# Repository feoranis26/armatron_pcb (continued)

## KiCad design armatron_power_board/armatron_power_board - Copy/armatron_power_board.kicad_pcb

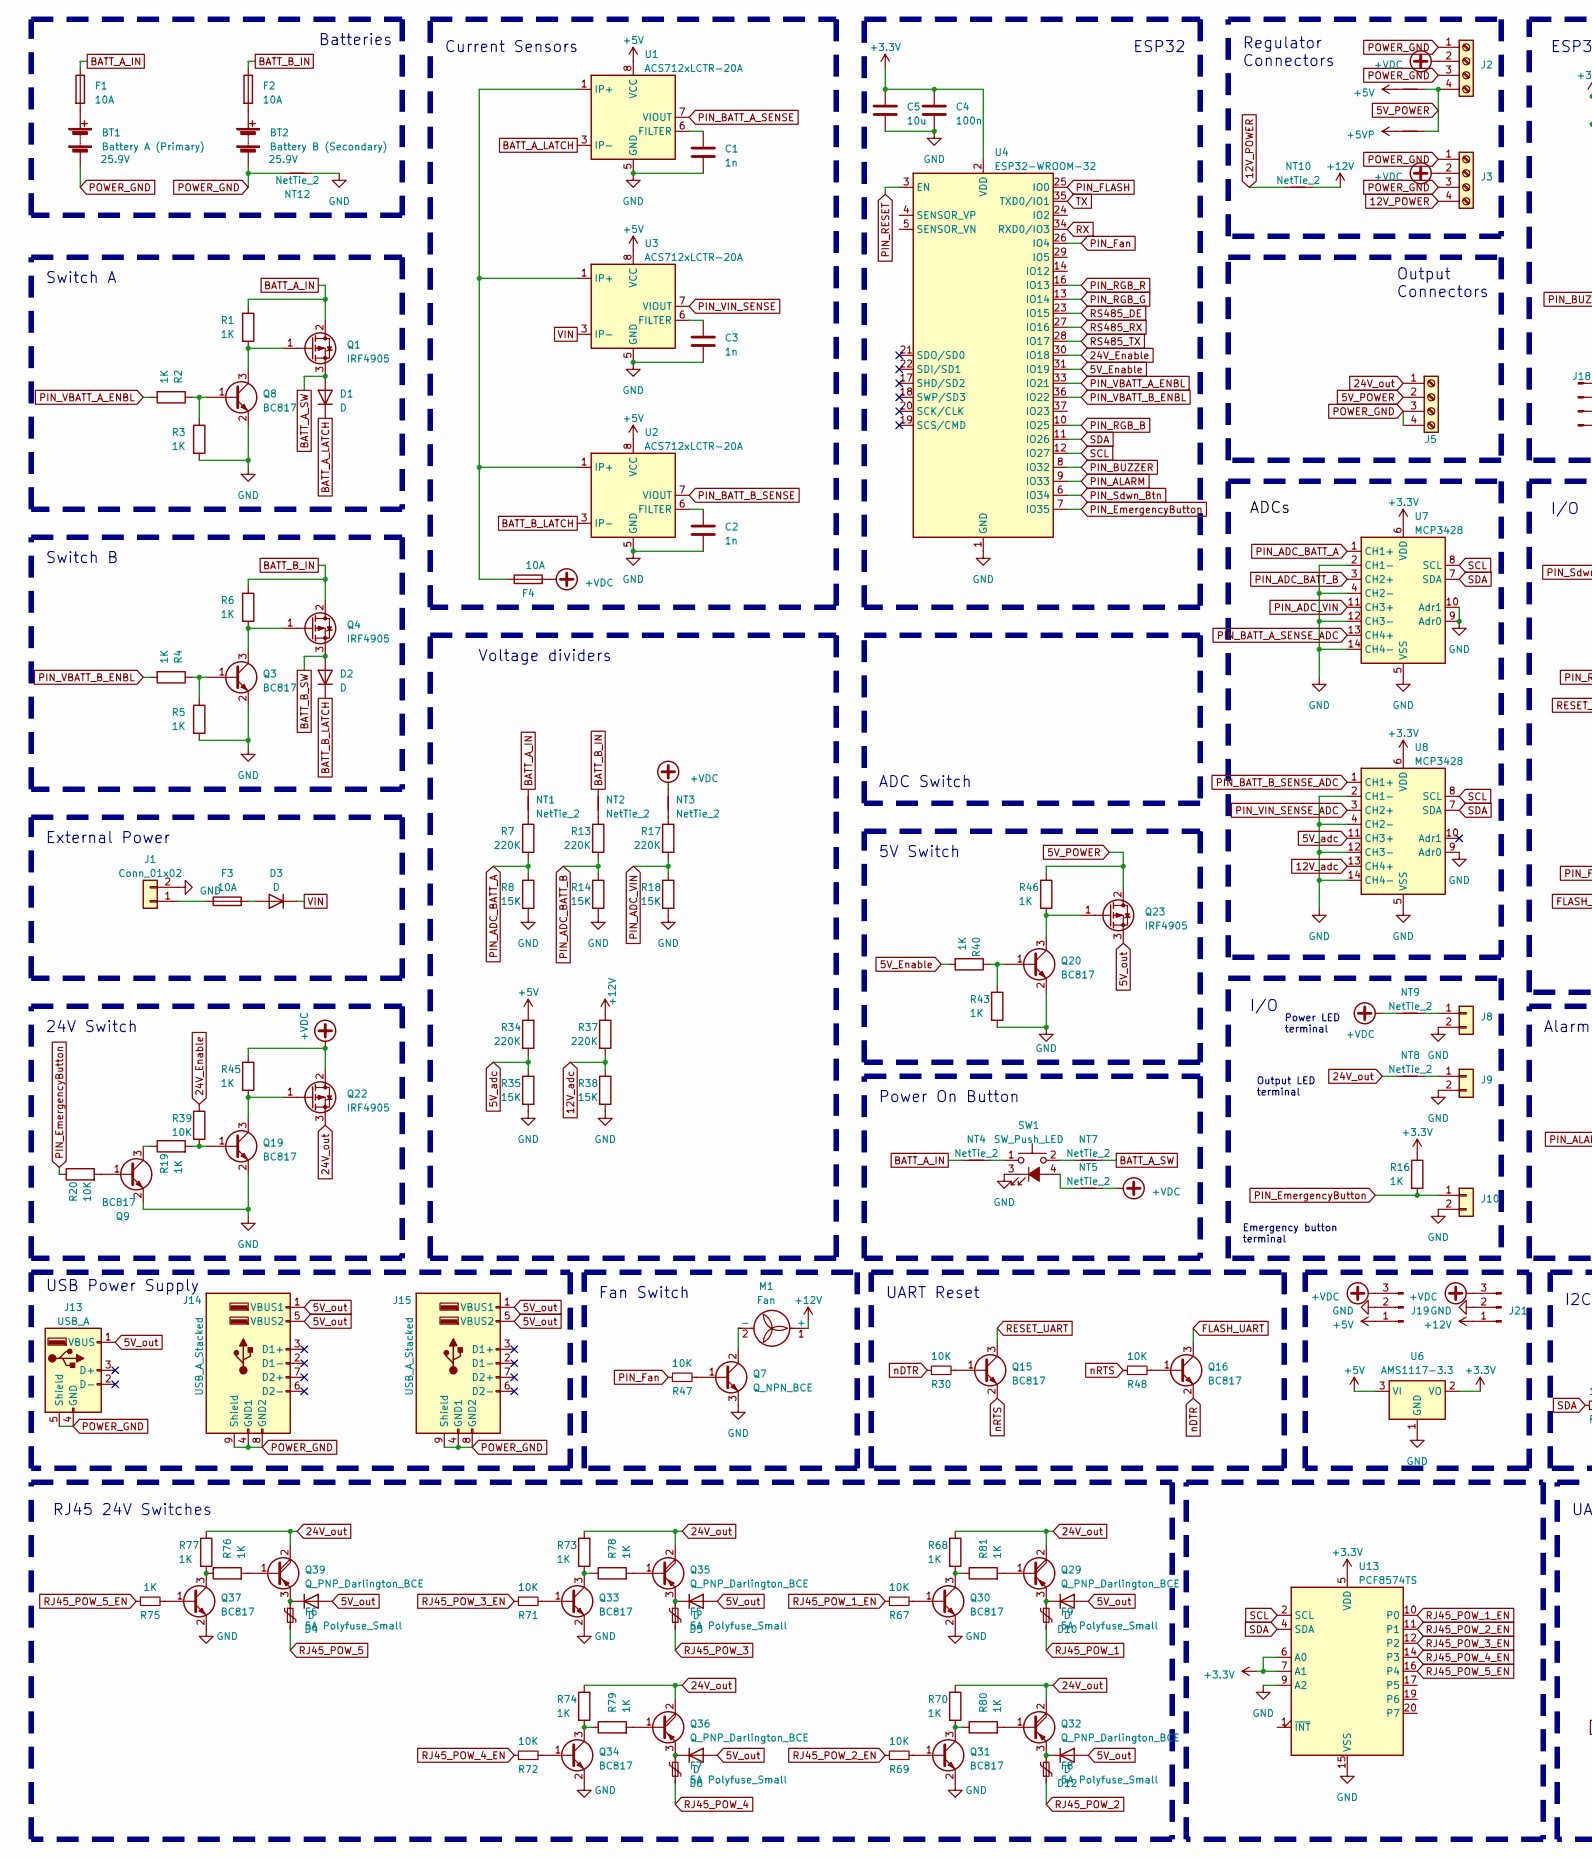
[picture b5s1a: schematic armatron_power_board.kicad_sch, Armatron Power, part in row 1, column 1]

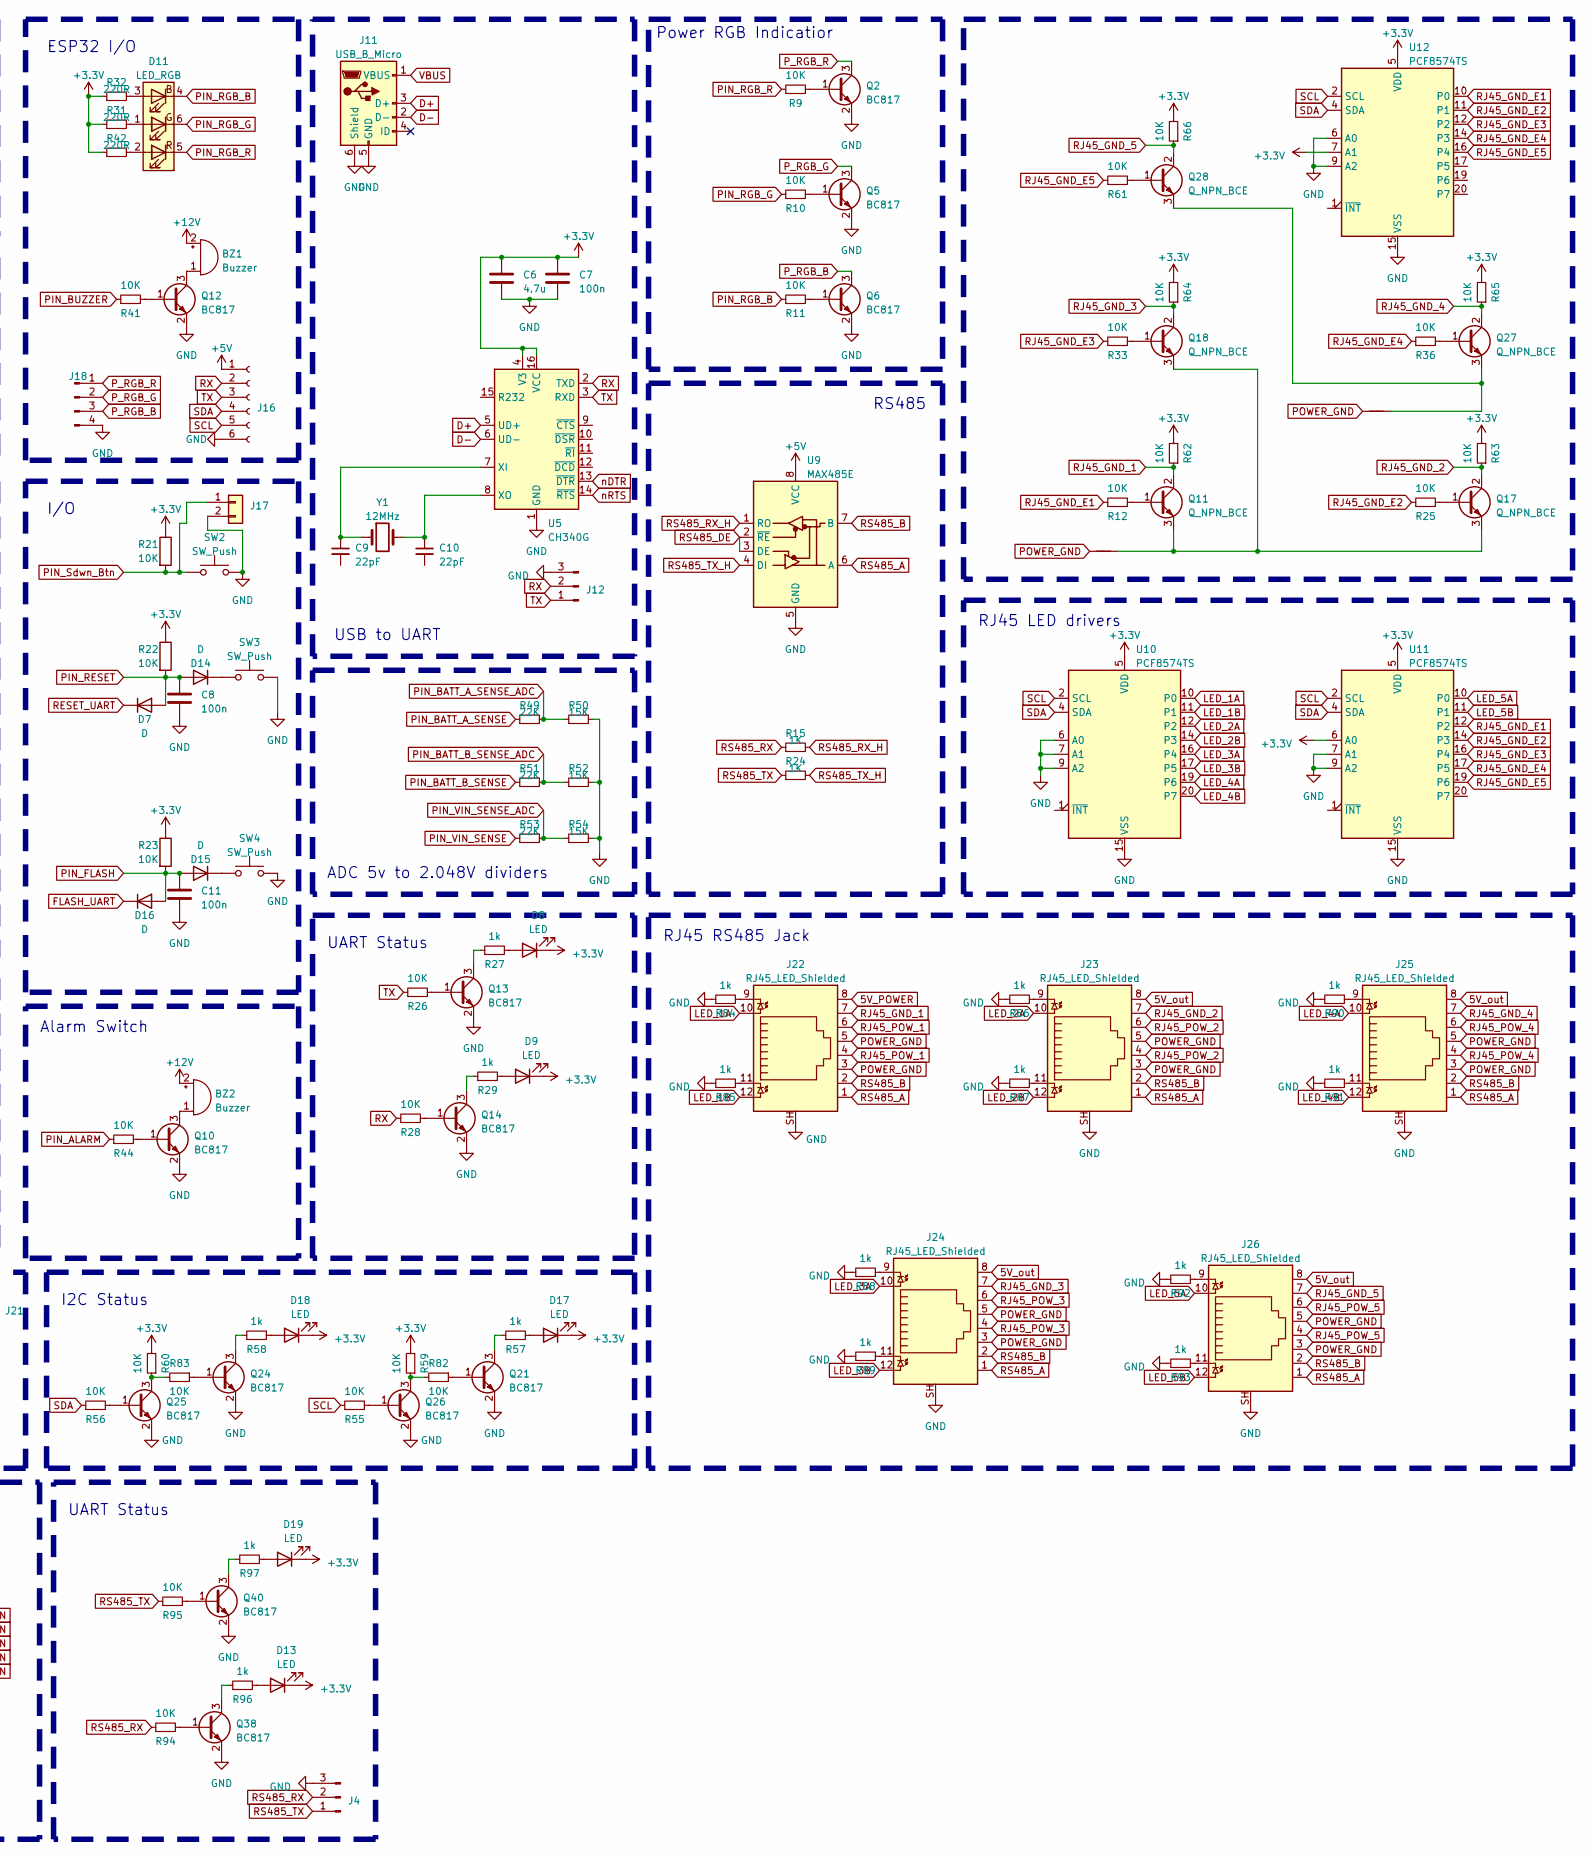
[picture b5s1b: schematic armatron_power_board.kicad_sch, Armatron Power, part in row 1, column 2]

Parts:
BT1: Battery A (Primary); TerminalBlock_bornier-2_P5.08mm; Voltage 25.9V
BT2: Battery B (Secondary); TerminalBlock_bornier-2_P5.08mm; Voltage 25.9V
BZ1, BZ2: Buzzer; PinHeader_1x02_P2.54mm_Vertical
C1, C2, C3: 1n; C_0805_2012Metric_Pad1.18x1.45mm_HandSolder
C4, C7, C8, C11: 100n; C_0805_2012Metric_Pad1.18x1.45mm_HandSolder
C5: 10u; C_0805_2012Metric_Pad1.18x1.45mm_HandSolder
C6: 4.7u; C_0805_2012Metric_Pad1.18x1.45mm_HandSolder
C9, C10: 22pF; C_0805_2012Metric_Pad1.18x1.45mm_HandSolder
D1, D2, D3: D; TO-277B
D4, D5, D6, D10, D12: D; D_SMB
D7, D14, D15, D16: D; D_0805_2012Metric
D8, D9, D13, D17, D18, D19: LED; LED_1206_3216Metric_Pad1.42x1.75mm_HandSolder
D11: LED_RGB; LED_RGB_5050-6
F1, F2, F3, F4: 10A; Fuseholder_Cylinder-5x20mm_Schurter_0031_8201_Horizontal_Op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
F5, F6, F7, F8, F9: 5A Polyfuse_Small; Fuse_1812_4532Metric_Pad1.30x3.40mm_HandSolder
J1: Conn_01x02; TerminalBlock_bornier-2_P5.08mm
J2, J3, J5: Screw_Terminal_01x04; TerminalBlock_bornier-4_P5.08mm
J4, J12, J19, J21: Conn_01x03_Pin; PinHeader_1x03_P2.54mm_Vertical
J8, J9, J10, J17: Conn_01x02; PinHeader_1x02_P2.54mm_Vertical
J11: USB_B_Micro; USB_Micro-B_Amphenol_10118194_Horizontal
J13: USB_A; USB_A_Molex_67643_Horizontal
J14, J15: USB_A_Stacked; USB_A_Wuerth_61400826021_Horizontal_Stacked
J16: Conn_01x06_Socket; PinSocket_1x06_P2.54mm_Vertical
J18: Conn_01x04_Pin; PinHeader_1x04_P2.54mm_Vertical
J22, J23, J24, J25, J26: RJ45_LED_Shielded; RJ45_Hanrun_HR911105A
M1: Fan; PinHeader_1x02_P2.54mm_Vertical
NT1, NT2, NT3, NT4, NT5, NT6, NT7, NT8, NT9, NT10, NT11, NT12, NT13, NT14: NetTie_2; NetTie-2_THT_Pad1.0mm
Q1, Q4, Q22, Q23: IRF4905; TO-263-2
Q2, Q3, Q5, Q6, Q8, Q9, Q10, Q12, Q13, Q14, Q15, Q16, Q19, Q20, Q21, Q24, Q25, Q26, Q30, Q31, Q33, Q34, Q37, Q38, Q40: BC817; SOT-23
Q7: Q_NPN_BCE; SOT-89-3_Handsoldering
Q11, Q17, Q18, Q27, Q28: Q_NPN_BCE; TO-252-2
Q29, Q32, Q35, Q36, Q39: Q_PNP_Darlington_BCE; TO-252-2
R1, R2, R3, R4, R5, R6, R15, R16, R19, R24, R40, R43, R45, R46, R68, R70, R73, R74, R75, R76, R77, R78, R79, R80, R81: 1K; R_0805_2012Metric_Pad1.20x1.40mm_HandSolder
R7, R13, R17, R34, R37: 220K; R_0805_2012Metric_Pad1.20x1.40mm_HandSolder
R8, R14, R18, R35, R38, R50, R52, R54: 15K; R_0805_2012Metric_Pad1.20x1.40mm_HandSolder
R9, R10, R11, R12, R20, R21, R22, R23, R25, R26, R28, R30, R33, R36, R39, R41, R44, R47, R48, R55, R56, R59, R60, R61, R62, R63, R64, R65, R66, R67, R69, R71, R72, R82, R83, R94, R95: 10K; R_0805_2012Metric_Pad1.20x1.40mm_HandSolder
R27, R29, R57, R58, R84, R85, R86, R87, R88, R89, R90, R91, R92, R93, R96, R97: 1k; R_0805_2012Metric_Pad1.20x1.40mm_HandSolder
R31, R32, R42: 220R; R_0805_2012Metric_Pad1.20x1.40mm_HandSolder
R49, R51, R53: 22K; R_0805_2012Metric_Pad1.20x1.40mm_HandSolder
SW1: SW_Push_LED; PinHeader_1x04_P2.54mm_Vertical
SW2, SW3, SW4: SW_Push; SW_SPST_TL3342
U1, U2, U3: ACS712xLCTR-20A; SOIC-8_3.9x4.9mm_P1.27mm
U4: ESP32-WROOM-32
U5: CH340G; SOIC-16_3.9x9.9mm_P1.27mm
U6: AMS1117-3.3; SOT-223-3_TabPin2
U7, U8: MCP3428; SOIC-14_3.9x8.7mm_P1.27mm
U9: MAX485E; SSOP-8_2.95x2.8mm_P0.65mm
U10, U11, U12, U13: PCF8574TS; PCF8574
Y1: 12MHz; Crystal_SMD_5032-2Pin_5.0x3.2mm_HandSoldering

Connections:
5V_Enable: R40.2, U4.31 (IO19)
5V_POWER: J2.4, J5.2, J22.8, NT6.2, NT11.2, Q23.2 (D), R46.1
5V_adc: R34.2, R35.1, U8.11 (CH3+)
5V_out: D4.2 (A), D5.2 (A), D6.2 (A), D10.2 (A), D12.2 (A), J13.1 (VBUS), J14.1 (VBUS1), J14.5 (VBUS2), J15.1 (VBUS1), J15.5 (VBUS2), J23.8, J24.8, J25.8, J26.8, Q23.3 (S)
12V_POWER: J3.4, NT10.1
12V_adc: R37.2, R38.1, U8.13 (CH4+)
24V_Enable: R39.1, U4.30 (IO18)
24V_out: J5.1, NT8.1, Q22.3 (S), Q29.2 (C), Q32.2 (C), Q35.2 (C), Q36.2 (C), Q39.2 (C), R68.1, R70.1, R73.1, R74.1, R77.1
+3.3V: C4.1, C5.1, C6.1, C7.1, D8.1 (K), D9.1 (K), D13.1 (K), D17.1 (K), D18.1 (K), D19.1 (K), R16.1, R21.1, R22.1, R23.1, R31.1, R32.1, R42.1, R59.2, R60.2, R62.2, R63.2, R64.2, R65.2, R66.2, U4.2 (VDD), U5.4 (V3), U5.16 (VCC), U6.2 (VO), U7.6 (VDD), U8.6 (VDD), U10.5 (VDD), U11.5 (VDD), U11.6 (A0), U12.5 (VDD), U12.7 (A1), U13.5 (VDD), U13.6 (A0), U13.7 (A1)
+5V: J16.1, J19.1, NT6.1, R34.1, U1.8 (VCC), U2.8 (VCC), U3.8 (VCC), U6.3 (VI), U9.8 (VCC)
+5VP: NT11.1
+12V: BZ1.2 (-), BZ2.2 (-), J21.1, M1.1 (+), NT10.2, R37.1
+VDC: F4.2, J2.2, J3.2, J19.3, J21.3, NT3.2, NT5.2, NT9.1, Q22.2 (D), R45.1
BATT_A_IN: F1.1, NT1.2, NT4.1, Q1.2 (D), R1.1
BATT_A_LATCH: D1.1 (K), U1.3 (IP-), U1.4 (IP-)
BATT_A_SW: D1.2 (A), NT7.2, Q1.3 (S)
BATT_B_IN: F2.1, NT2.2, Q4.2 (D), R6.1
BATT_B_LATCH: D2.1 (K), U2.3 (IP-), U2.4 (IP-)
BATT_B_SW: D2.2 (A), Q4.3 (S)
D+: J11.3 (D+), U5.5 (UD+)
D-: J11.2 (D-), U5.6 (UD-)
FLASH_UART: D16.1 (K), Q16.3 (C)
GND: C1.2, C2.2, C3.2, C4.2, C5.2, C6.2, C7.2, C8.2, C11.2, J1.2, J4.3, J8.2, J9.2, J10.2, J11.5 (GND), J11.6 (Shield), J12.3, J16.6, J17.2, J18.4, J19.2, J21.2, J22.SH, J23.SH, J24.SH, J25.SH, J26.SH, NT12.1, Q2.2 (E), Q3.2 (E), Q5.2 (E), Q6.2 (E), Q7.3 (E), Q8.2 (E), Q9.2 (E), Q10.2 (E), Q12.2 (E), Q13.2 (E), Q14.2 (E), Q19.2 (E), Q20.2 (E), Q21.2 (E), Q24.2 (E), Q25.2 (E), Q26.2 (E), Q30.2 (E), Q31.2 (E), Q33.2 (E), Q34.2 (E), Q37.2 (E), Q38.2 (E), Q40.2 (E), R3.2, R5.2, R8.2, R14.2, R18.2, R35.2, R38.2, R43.2, R50.2, R52.2, R54.2, R84.1, R85.1, R86.1, R87.1, R88.1, R89.1, R90.1, R91.1, R92.1, R93.1, SW1.3 (K), SW2.2, SW3.2, SW4.2, U1.5 (GND), U2.5 (GND), U3.5 (GND), U4.1 (GND), U4.15 (GND), U4.38 (GND), U4.39 (GND), U5.1 (GND), U6.1 (GND), U7.2 (CH1-), U7.4 (CH2-), U7.5 (VSS), U7.9 (Adr0), U7.10 (Adr1), U7.12 (CH3-), U7.14 (CH4-), U8.2 (CH1-), U8.4 (CH2-), U8.5 (VSS), U8.9 (Adr0), U8.12 (CH3-), U8.14 (CH4-), U9.5 (GND), U10.6 (A0), U10.7 (A1), U10.9 (A2), U10.15 (VSS), U11.7 (A1), U11.9 (A2), U11.15 (VSS), U12.6 (A0), U12.9 (A2), U12.15 (VSS), U13.9 (A2), U13.15 (VSS)
LED_1A: J22.10, U10.10 (P0)
LED_1B: J22.12, U10.11 (P1)
LED_2A: J23.10, U10.12 (P2)
LED_2B: J23.12, U10.14 (P3)
LED_3A: J24.10, U10.16 (P4)
LED_3B: J24.12, U10.17 (P5)
LED_4A: J25.10, U10.19 (P6)
LED_4B: J25.12, U10.20 (P7)
LED_5A: J26.10, U11.10 (P0)
LED_5B: J26.12, U11.11 (P1)
unnamed: BT1.1 (+), F1.2
unnamed: BT2.1 (+), F2.2
unnamed: BZ1.1 (+), Q12.3 (C)
unnamed: BZ2.1 (+), Q10.3 (C)
unnamed: D3.2 (A), F3.2
unnamed: D4.1 (K), F6.1, Q39.3 (E)
unnamed: D5.1 (K), F5.1, Q35.3 (E)
unnamed: D6.1 (K), F7.1, Q36.3 (E)
unnamed: D8.2 (A), R27.2
unnamed: D9.2 (A), R29.2
unnamed: D10.1 (K), F9.1, Q29.3 (E)
unnamed: D11.3 (BA), R32.2
unnamed: D11.1 (GA), R31.2
unnamed: D11.2 (RA), R42.2
unnamed: D12.1 (K), F8.1, Q32.3 (E)
unnamed: D13.2 (A), R96.2
unnamed: D14.1 (K), SW3.1
unnamed: D15.1 (K), SW4.1
unnamed: D17.2 (A), R57.2
unnamed: D18.2 (A), R58.2
unnamed: D19.2 (A), R97.2
unnamed: F4.1, U1.1 (IP+), U1.2 (IP+), U2.1 (IP+), U2.2 (IP+), U3.1 (IP+), U3.2 (IP+)
unnamed: F3.1, J1.1
unnamed: J8.1, NT9.2
unnamed: J9.1, NT8.2
unnamed: J22.9, R84.2
unnamed: J22.11, R85.2
unnamed: J23.9, R86.2
unnamed: J23.11, R87.2
unnamed: J24.9, R88.2
unnamed: J24.11, R89.2
unnamed: J25.9, R90.2
unnamed: J25.11, R91.2
unnamed: J26.9, R92.2
unnamed: J26.11, R93.2
unnamed: M1.2 (-), Q7.2 (C)
unnamed: NT1.1, R7.1
unnamed: NT2.1, R13.1
unnamed: NT3.1, R17.1
unnamed: NT4.2, SW1.1
unnamed: NT7.1, SW1.2
unnamed: Q1.1 (G), Q8.3 (C), R1.2
unnamed: Q2.1 (B), R9.2
unnamed: Q3.1 (B), R4.1, R5.1
unnamed: Q3.3 (C), Q4.1 (G), R6.2
unnamed: Q5.1 (B), R10.2
unnamed: Q6.1 (B), R11.2
unnamed: Q7.1 (B), R47.2
unnamed: Q8.1 (B), R2.1, R3.1
unnamed: Q9.1 (B), R20.2
unnamed: Q9.3 (C), R19.1
unnamed: Q10.1 (B), R44.2
unnamed: Q11.1 (B), R12.2
unnamed: NT13.1, Q11.3 (E), Q17.3 (E), Q18.3 (E)
unnamed: Q12.1 (B), R41.2
unnamed: Q13.1 (B), R26.2
unnamed: Q13.3 (C), R27.1
unnamed: Q14.1 (B), R28.2
unnamed: Q14.3 (C), R29.1
unnamed: Q15.1 (B), R30.2
unnamed: Q16.1 (B), R48.2
unnamed: Q17.1 (B), R25.2
unnamed: Q18.1 (B), R33.2
unnamed: Q19.1 (B), R19.2, R39.2
unnamed: Q19.3 (C), Q22.1 (G), R45.2
unnamed: Q20.1 (B), R40.1, R43.1
unnamed: Q20.3 (C), Q23.1 (G), R46.2
unnamed: Q21.1 (B), R82.1
unnamed: Q21.3 (C), R57.1
unnamed: Q24.1 (B), R83.1
unnamed: Q24.3 (C), R58.1
unnamed: Q25.1 (B), R56.2
unnamed: Q25.3 (C), R60.1, R83.2
unnamed: Q26.1 (B), R55.2
unnamed: Q26.3 (C), R59.1, R82.2
unnamed: Q27.1 (B), R36.2
unnamed: NT14.1, Q27.3 (E), Q28.3 (E)
unnamed: Q28.1 (B), R61.2
unnamed: Q29.1 (B), R81.2
unnamed: Q30.1 (B), R67.2
unnamed: Q30.3 (C), R68.2, R81.1
unnamed: Q31.1 (B), R69.2
unnamed: Q31.3 (C), R70.2, R80.1
unnamed: Q32.1 (B), R80.2
unnamed: Q33.1 (B), R71.2
unnamed: Q33.3 (C), R73.2, R78.1
unnamed: Q34.1 (B), R72.2
unnamed: Q34.3 (C), R74.2, R79.1
unnamed: Q35.1 (B), R78.2
unnamed: Q36.1 (B), R79.2
unnamed: Q37.1 (B), R75.2
unnamed: Q37.3 (C), R76.1, R77.2
unnamed: Q38.1 (B), R94.2
unnamed: Q38.3 (C), R96.1
unnamed: Q39.1 (B), R76.2
unnamed: Q40.1 (B), R95.2
unnamed: Q40.3 (C), R97.1
unnamed: NT5.1, SW1.4 (A)
unnamed: C1.1, U1.6 (FILTER)
unnamed: C2.1, U2.6 (FILTER)
unnamed: C3.1, U3.6 (FILTER)
unnamed: C9.1, U5.7 (XI), Y1.1
unnamed: C10.1, U5.8 (XO), Y1.2
PIN_ADC_BATT_A: R7.2, R8.1, U7.1 (CH1+)
PIN_ADC_BATT_B: R13.2, R14.1, U7.3 (CH2+)
PIN_ADC_VIN: R17.2, R18.1, U7.11 (CH3+)
PIN_ALARM: R44.1, U4.9 (IO33)
PIN_BATT_A_SENSE: R49.1, U1.7 (VIOUT)
PIN_BATT_A_SENSE_ADC: R49.2, R50.1, U7.13 (CH4+)
PIN_BATT_B_SENSE: R51.1, U2.7 (VIOUT)
PIN_BATT_B_SENSE_ADC: R51.2, R52.1, U8.1 (CH1+)
PIN_BUZZER: R41.1, U4.8 (IO32)
PIN_EmergencyButton: J10.1, R16.2, R20.1, U4.7 (IO35)
PIN_FLASH: C11.1, D15.2 (A), D16.2 (A), R23.2, U4.25 (IO0)
PIN_Fan: R47.1, U4.26 (IO4)
PIN_RESET: C8.1, D7.2 (A), D14.2 (A), R22.2, U4.3 (EN)
PIN_RGB_B: D11.4 (BK), R11.1, U4.10 (IO25)
PIN_RGB_G: D11.6 (GK), R10.1, U4.13 (IO14)
PIN_RGB_R: D11.5 (RK), R9.1, U4.16 (IO13)
PIN_Sdwn_Btn: J17.1, R21.2, SW2.1, U4.6 (IO34)
PIN_VBATT_A_ENBL: R2.2, U4.33 (IO21)
PIN_VBATT_B_ENBL: R4.2, U4.36 (IO22)
PIN_VIN_SENSE: R53.1, U3.7 (VIOUT)
PIN_VIN_SENSE_ADC: R53.2, R54.1, U8.3 (CH2+)
POWER_GND: BT1.2 (-), BT2.2 (-), J2.1, J2.3, J3.1, J3.3, J5.3, J5.4, J13.4 (GND), J13.5 (Shield), J14.4 (GND1), J14.8 (GND2), J14.9 (Shield), J15.4 (GND1), J15.8 (GND2), J15.9 (Shield), J22.3, J22.5, J23.3, J23.5, J24.3, J24.5, J25.3, J25.5, J26.3, J26.5, NT12.2, NT13.2, NT14.2
P_RGB_B: J18.3, Q6.3 (C)
P_RGB_G: J18.2, Q5.3 (C)
P_RGB_R: J18.1, Q2.3 (C)
RESET_UART: D7.1 (K), Q15.3 (C)
RJ45_GND_1: J22.7, Q11.2 (C), R62.1
RJ45_GND_2: J23.7, Q17.2 (C), R63.1
RJ45_GND_3: J24.7, Q18.2 (C), R64.1
RJ45_GND_4: J25.7, Q27.2 (C), R65.1
RJ45_GND_5: J26.7, Q28.2 (C), R66.1
RJ45_GND_E1: R12.1, U11.12 (P2), U12.10 (P0)
RJ45_GND_E2: R25.1, U11.14 (P3), U12.11 (P1)
RJ45_GND_E3: R33.1, U11.16 (P4), U12.12 (P2)
RJ45_GND_E4: R36.1, U11.17 (P5), U12.14 (P3)
RJ45_GND_E5: R61.1, U11.19 (P6), U12.16 (P4)
RJ45_POW_1: F9.2, J22.4, J22.6
RJ45_POW_1_EN: R67.1, U13.10 (P0)
RJ45_POW_2: F8.2, J23.4, J23.6
RJ45_POW_2_EN: R69.1, U13.11 (P1)
RJ45_POW_3: F5.2, J24.4, J24.6
RJ45_POW_3_EN: R71.1, U13.12 (P2)
RJ45_POW_4: F7.2, J25.4, J25.6
RJ45_POW_4_EN: R72.1, U13.14 (P3)
RJ45_POW_5: F6.2, J26.4, J26.6
RJ45_POW_5_EN: R75.1, U13.16 (P4)
RS485_A: J22.1, J23.1, J24.1, J25.1, J26.1, U9.6 (A)
RS485_B: J22.2, J23.2, J24.2, J25.2, J26.2, U9.7 (B)
RS485_DE: U4.23 (IO15), U9.2 (~RE), U9.3 (DE)
RS485_RX: J4.2, R15.1, R94.1, U4.27 (IO16)
RS485_RX_H: R15.2, U9.1 (RO)
RS485_TX: J4.1, R24.1, R95.1, U4.28 (IO17)
RS485_TX_H: R24.2, U9.4 (DI)
RX: J12.2, J16.2, R28.1, U4.34 (RXD0/IO3), U5.2 (TXD)
SCL: J16.5, R55.1, U4.12 (IO27), U7.8 (SCL), U8.8 (SCL), U10.2 (SCL), U11.2 (SCL), U12.2 (SCL), U13.2 (SCL)
SDA: J16.4, R56.1, U4.11 (IO26), U7.7 (SDA), U8.7 (SDA), U10.4 (SDA), U11.4 (SDA), U12.4 (SDA), U13.4 (SDA)
TX: J12.1, J16.3, R26.1, U4.35 (TXD0/IO1), U5.3 (RXD)
VBUS: J11.1 (VBUS)
VIN: D3.1 (K), U3.3 (IP-), U3.4 (IP-)
nDTR: Q16.2 (E), R30.1, U5.13 (~DTR)
nRTS: Q15.2 (E), R48.1, U5.14 (~RTS)

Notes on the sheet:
ADC Switch
I/O
Fan Switch
External Power
24V Switch
ESP32
USB to UART
Emergency button terminal
RJ45 RS485 Jack
ADC 5v to 2.048V dividers
I2C Status
ESP32 I/O
Regulator Connectors
Output LED terminal
Switch B
RS485
Power RGB Indicatior
RJ45 LED drivers
USB Power Supply
Power On Button
Voltage dividers
UART Status
5V Switch
Alarm Switch
RJ45 24V Switches
Power LED terminal
Output Connectors
Current Sensors
Batteries
Switch A
UART Reset

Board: 4 copper layers, 240 parts (123 on the bottom side), 195 nets, no tracks yet.

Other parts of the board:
MH1, MH2, MH3, MH4: MountingHole_3.2mm_M3

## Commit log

2023-11-28 initial
